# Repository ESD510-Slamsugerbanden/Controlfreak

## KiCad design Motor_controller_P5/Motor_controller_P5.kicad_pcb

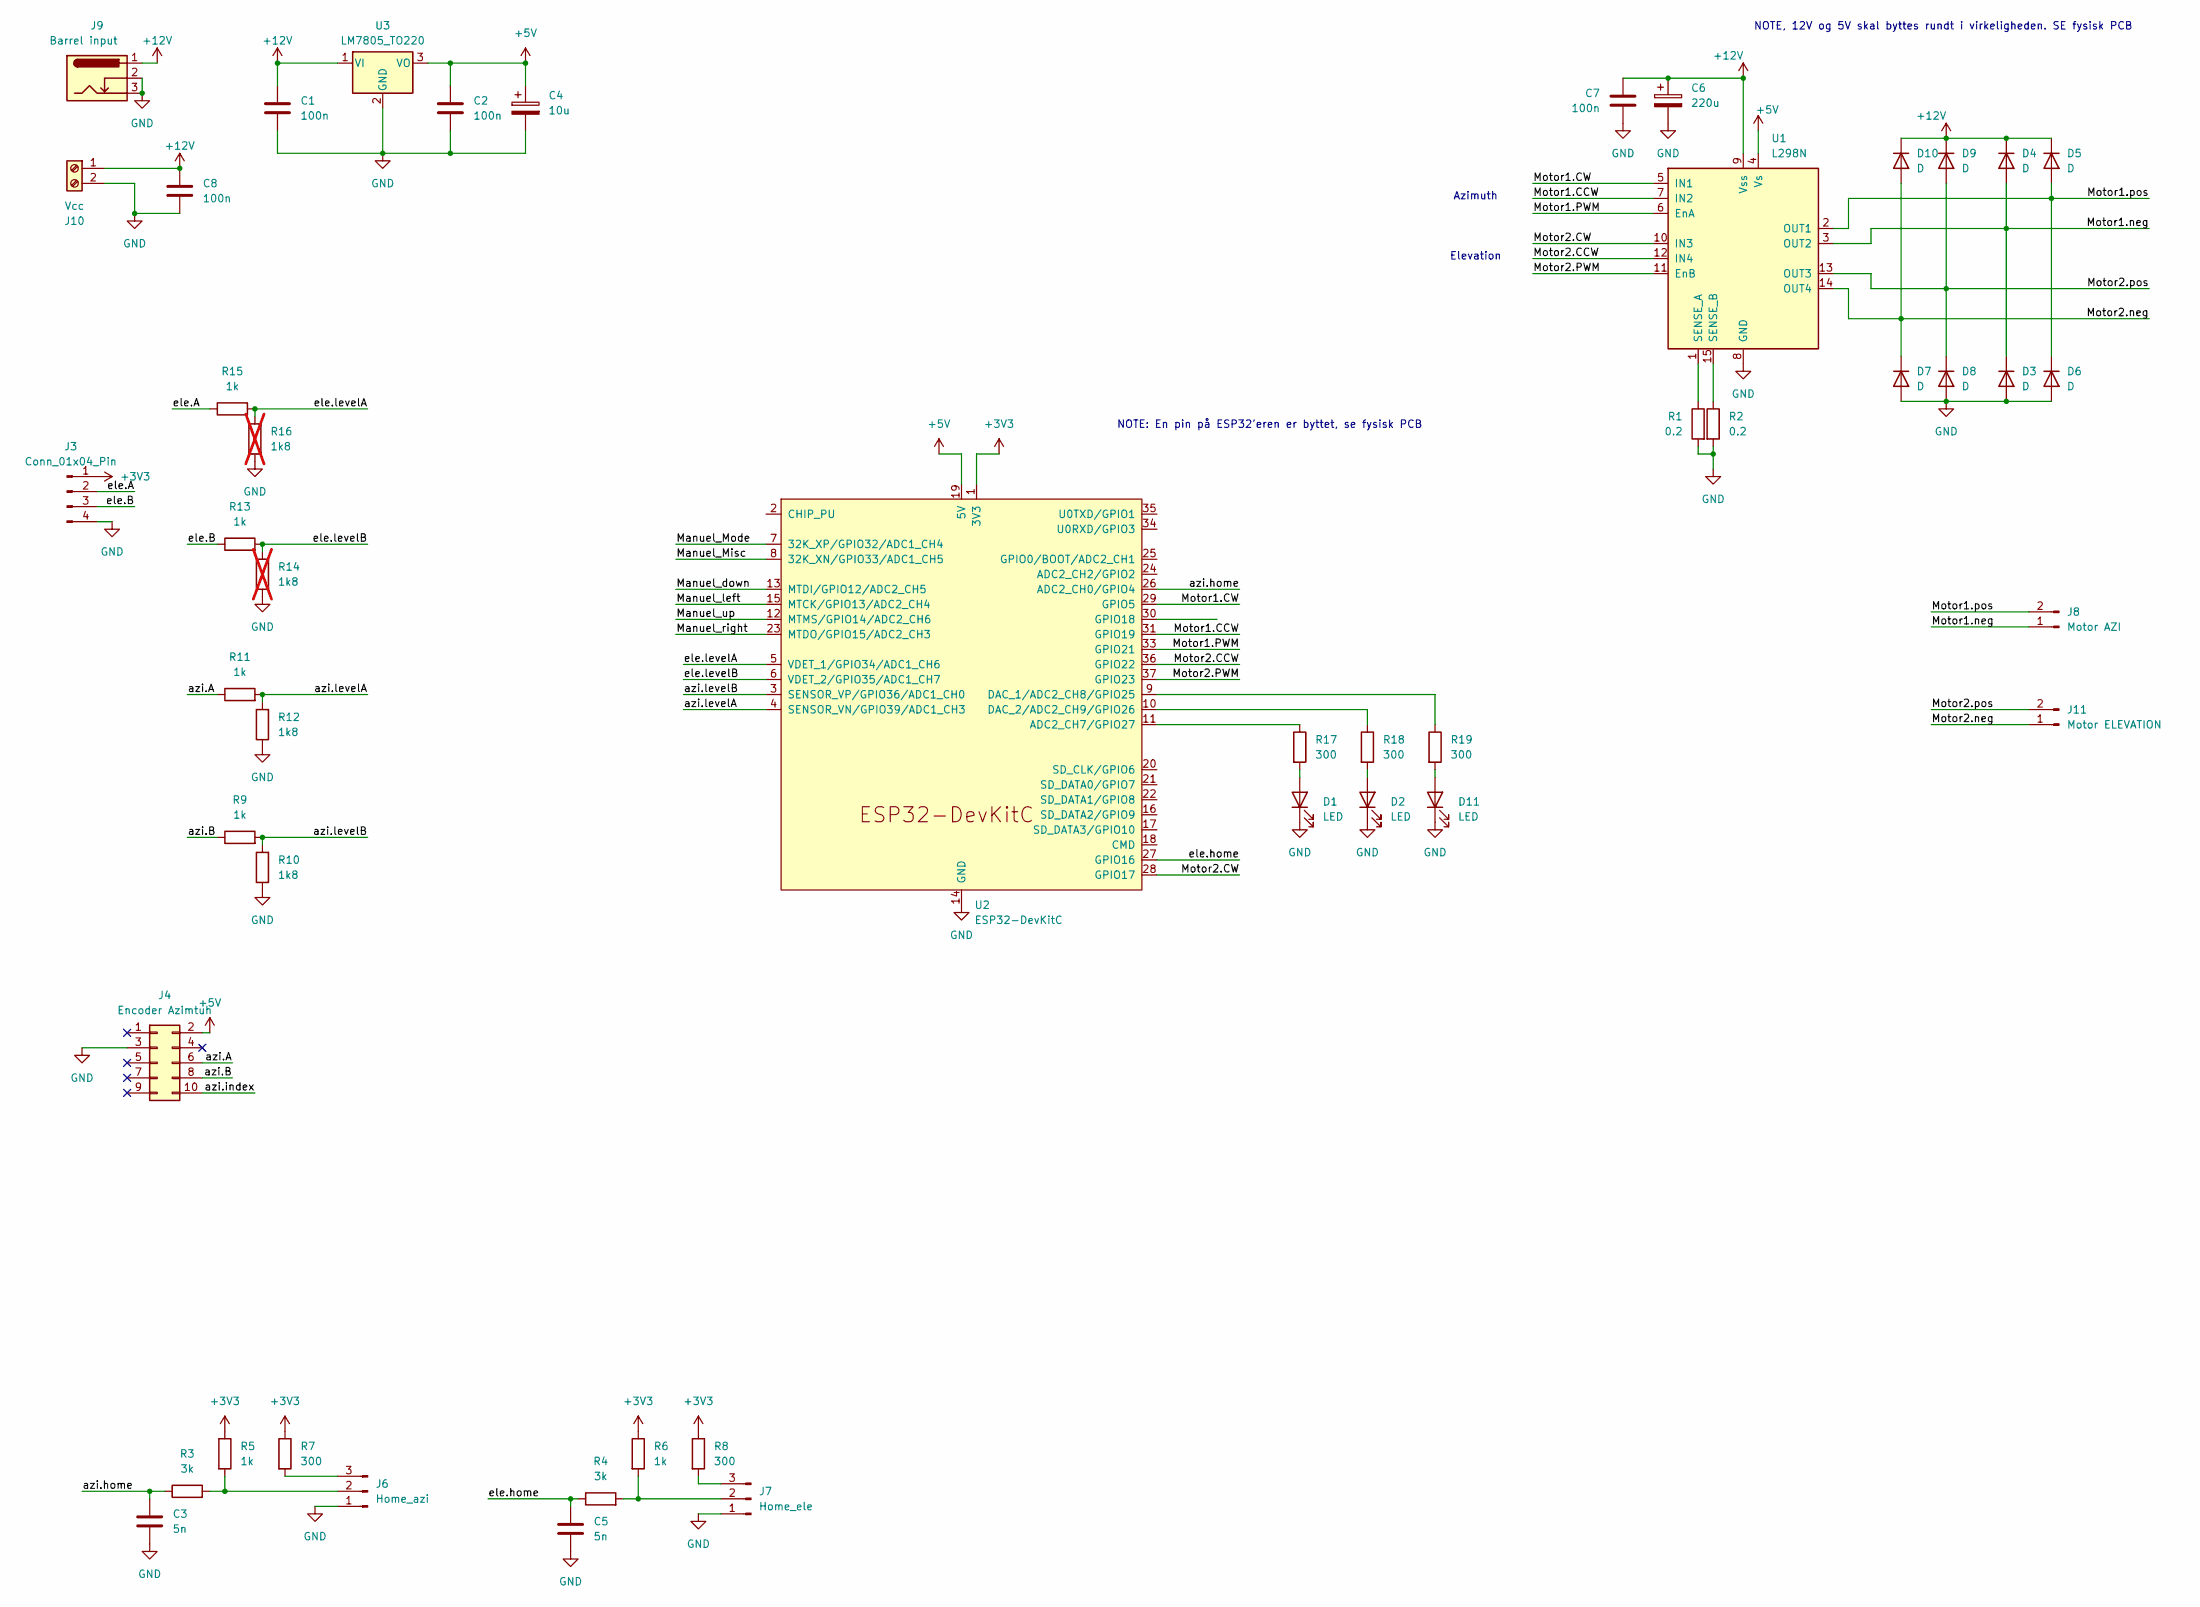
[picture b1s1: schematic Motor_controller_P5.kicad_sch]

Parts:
C1, C2: 100n; C_Rect_L7.0mm_W3.5mm_P5.00mm
C3, C5: 5n; C_Rect_L7.0mm_W2.5mm_P5.00mm
C4: 10u; CP_Radial_D5.0mm_P2.50mm
C6: 220u; CP_Radial_D8.0mm_P5.00mm
C7: 100n; C_0805_2012Metric_Pad1.18x1.45mm_HandSolder
C8: 100n; C_Rect_L7.0mm_W2.5mm_P5.00mm
D1, D2, D11: LED; LED_D5.0mm_Horizontal_O1.27mm_Z3.0mm
D3, D4, D5, D6, D7, D8, D9, D10: D; D_A-405_P7.62mm_Horizontal
J3: Conn_01x04_Pin; JST_XH_B4B-XH-AM_1x04_P2.50mm_Vertical
J4: Encoder Azimtuh; IDC-Header_2x05_P2.54mm_Vertical
J6: Home_azi; JST_EH_B3B-EH-A_1x03_P2.50mm_Vertical
J7: Home_ele; JST_EH_B3B-EH-A_1x03_P2.50mm_Vertical
J8: Motor AZI; JST_XH_B2B-XH-A_1x02_P2.50mm_Vertical
J9: Barrel input; BarrelJack_Horizontal
J10: Vcc; TerminalBlock_Phoenix_MKDS-1,5-2-5.08_1x02_P5.08mm_Horizont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
J11: Motor ELEVATION; JST_XH_B2B-XH-A_1x02_P2.50mm_Vertical
R1, R2: 0.2; R_Axial_DIN0614_L14.3mm_D5.7mm_P20.32mm_Horizontal
R3, R4: 3k; R_Axial_DIN0207_L6.3mm_D2.5mm_P7.62mm_Horizontal
R5, R6: 1k; R_Axial_DIN0207_L6.3mm_D2.5mm_P7.62mm_Horizontal
R7, R8: 300; R_Axial_DIN0207_L6.3mm_D2.5mm_P7.62mm_Horizontal
R9, R11, R13, R15: 1k; R_0603_1608Metric
R10, R12: 1k8; R_0603_1608Metric
R14, R16: 1k8; R_0603_1608Metric; not fitted
R17, R18, R19: 300; R_0805_2012Metric_Pad1.20x1.40mm_HandSolder
U1: L298N; TO-220-15_P2.54x5.08mm_StaggerOdd_Lead4.58mm_Vertical
U2: ESP32-DevKitC
U3: LM7805_TO220; TO-220-3_Vertical

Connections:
+3V3: J3.1, R5.1, R6.1, R7.1, R8.1, U2.1 (3V3)
+5V: C2.1, C4.1, J4.2, U1.4 (Vs), U2.19 (5V), U3.3 (VO)
+12V: C1.1, C6.1, C7.1, C8.1, D4.1 (K), D5.1 (K), D9.1 (K), D10.1 (K), J9.1, J10.1, U1.9 (Vss), U3.1 (VI)
/Manuel_Misc: U2.8 (32K_XN/GPIO33/ADC1_CH5)
/Manuel_Mode: U2.7 (32K_XP/GPIO32/ADC1_CH4)
/Manuel_down: U2.13 (MTDI/GPIO12/ADC2_CH5)
/Manuel_left: U2.15 (MTCK/GPIO13/ADC2_CH4)
/Manuel_right: U2.23 (MTDO/GPIO15/ADC2_CH3)
/Manuel_up: U2.12 (MTMS/GPIO14/ADC2_CH6)
/Motor1.CCW: U1.7 (IN2), U2.31 (GPIO19)
/Motor1.CW: U1.5 (IN1), U2.29 (GPIO5)
/Motor1.PWM: U1.6 (EnA), U2.33 (GPIO21)
/Motor1.neg: D3.1 (K), D4.2 (A), J8.1, U1.3 (OUT2)
/Motor1.pos: D5.2 (A), D6.1 (K), J8.2, U1.2 (OUT1)
/Motor2.CCW: U1.12 (IN4), U2.36 (GPIO22)
/Motor2.CW: U1.10 (IN3), U2.28 (GPIO17)
/Motor2.PWM: U1.11 (EnB), U2.37 (GPIO23)
/Motor2.neg: D7.1 (K), D10.2 (A), J11.1, U1.14 (OUT4)
/Motor2.pos: D8.1 (K), D9.2 (A), J11.2, U1.13 (OUT3)
/azi.A: J4.6, R11.1
/azi.B: J4.8, R9.1
/azi.home: C3.1, R3.1, U2.26 (ADC2_CH0/GPIO4)
/azi.index: J4.10
/azi.levelA: R11.2, R12.2, U2.4 (SENSOR_VN/GPIO39/ADC1_CH3)
/azi.levelB: R9.2, R10.2, U2.3 (SENSOR_VP/GPIO36/ADC1_CH0)
/ele.A: J3.2, R15.1
/ele.B: J3.3, R13.1
/ele.home: C5.1, R4.1, U2.27 (GPIO16)
/ele.levelA: R15.2, R16.2, U2.5 (VDET_1/GPIO34/ADC1_CH6)
/ele.levelB: R13.2, R14.2, U2.6 (VDET_2/GPIO35/ADC1_CH7)
GND: C1.2, C2.2, C3.2, C4.2, C5.2, C6.2, C7.2, C8.2, D1.1 (K), D2.1 (K), D3.2 (A), D6.2 (A), D7.2 (A), D8.2 (A), D11.1 (K), J3.4, J4.3, J6.1, J7.1, J9.2, J9.3, J10.2, R1.2, R2.2, R10.1, R12.1, R14.1, R16.1, U1.8 (GND), U2.14 (GND), U2.32 (GND), U2.38 (GND), U3.2 (GND)
unnamed: D1.2 (A), R17.2
unnamed: D2.2 (A), R18.2
unnamed: D11.2 (A), R19.2
unnamed: J6.2, R3.2, R5.2
unnamed: J6.3, R7.2
unnamed: J7.2, R4.2, R6.2
unnamed: J7.3, R8.2
unnamed: R1.1, U1.1 (SENSE_A)
unnamed: R2.1, U1.15 (SENSE_B)
unnamed: R17.1, U2.11 (ADC2_CH7/GPIO27)
unnamed: R19.1, U2.9 (DAC_1/ADC2_CH8/GPIO25)
unnamed: R18.1, U2.10 (DAC_2/ADC2_CH9/GPIO26)

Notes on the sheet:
NOTE, 12V og 5V skal byttes rundt i virkeligheden. SE fysisk PCB
NOTE: En pin på ESP32'eren er byttet, se fysisk PCB
Azimuth
Elevation

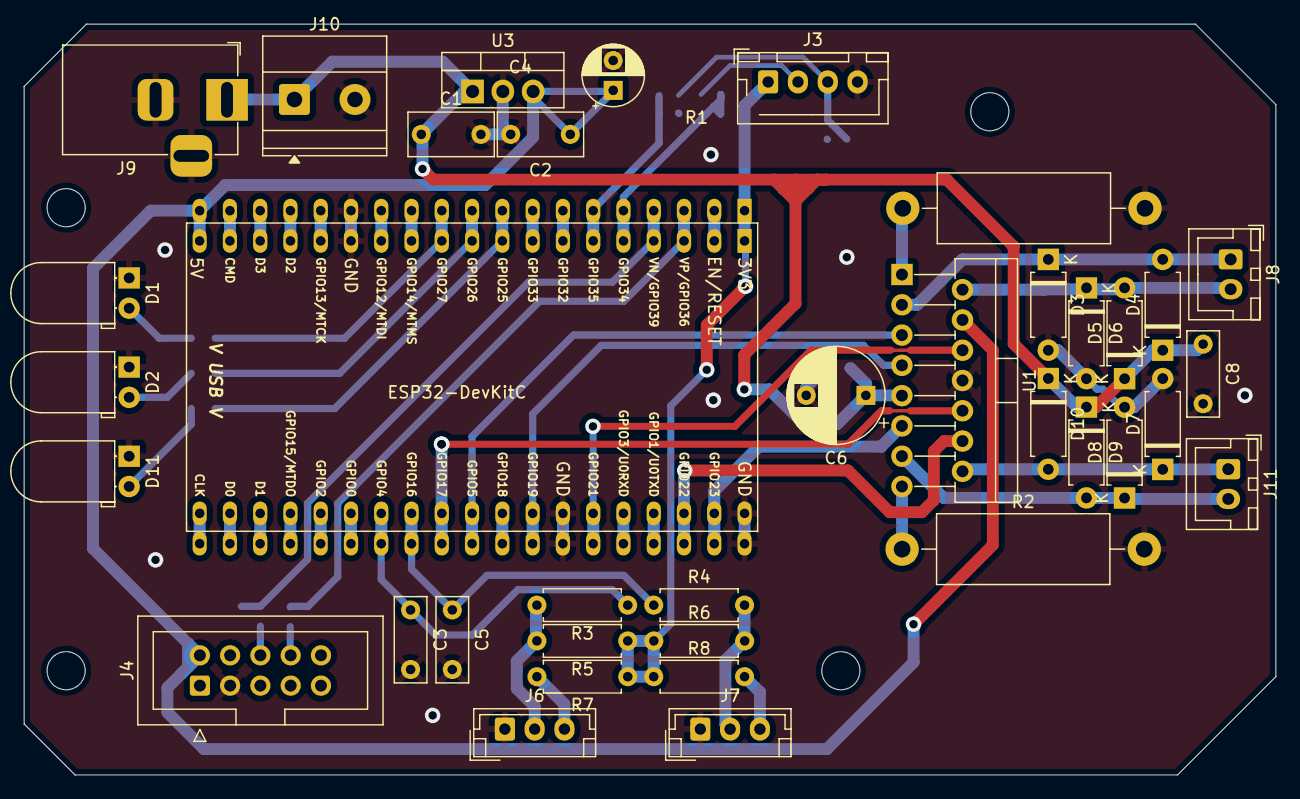
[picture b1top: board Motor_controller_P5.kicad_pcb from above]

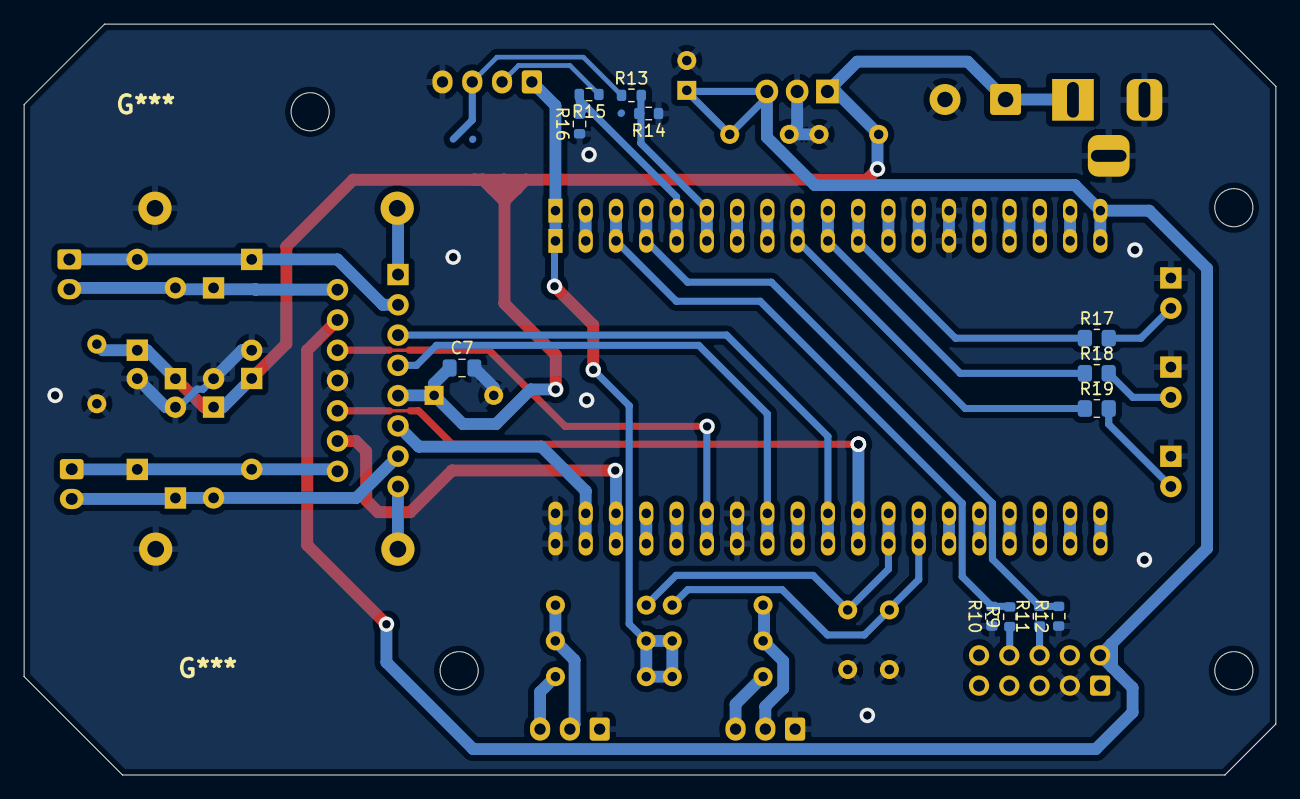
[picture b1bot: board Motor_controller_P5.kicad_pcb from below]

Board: 2 copper layers, 105.0 x 63.0 mm, 49 parts (12 on the bottom side), 36 nets.

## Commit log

2025-10-10 Driver with socket for UDP interface
2025-10-13 Converte to degs, and tigher control
2025-10-21 Blandet lort
2025-10-29 Serial der virker
2025-11-05 Ezcom fix
2025-11-11 kicad ting
2025-11-11 Alt det Axel har pillet ved...
2025-11-11 Prøv Mikkel
2025-11-11 Fix fax, platformIO.ini
2025-11-11 Virker flot
2025-11-14 Ændret hvad den skriver ud når den er i 0
2025-11-17 Converted to potmeter encoder
2025-11-18 Ikke meget nyt. Kun potmeter er korretk
2025-11-18 Dumme PID
2025-11-19 pid DONE Ikke kønt, men virker tilnærmelsesvist
2025-11-19 Removed serial print
2025-11-21 Flottede lige schematic
2025-11-21 ADDed comment to remember correct PID param
2025-12-01 Changed the count
2025-12-11 Drift fix
